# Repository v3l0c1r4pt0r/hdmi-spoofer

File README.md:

# HDMI EDID spoofer

Tiny HDMI board that optionally spoofs EDID data with contents of its own memory.

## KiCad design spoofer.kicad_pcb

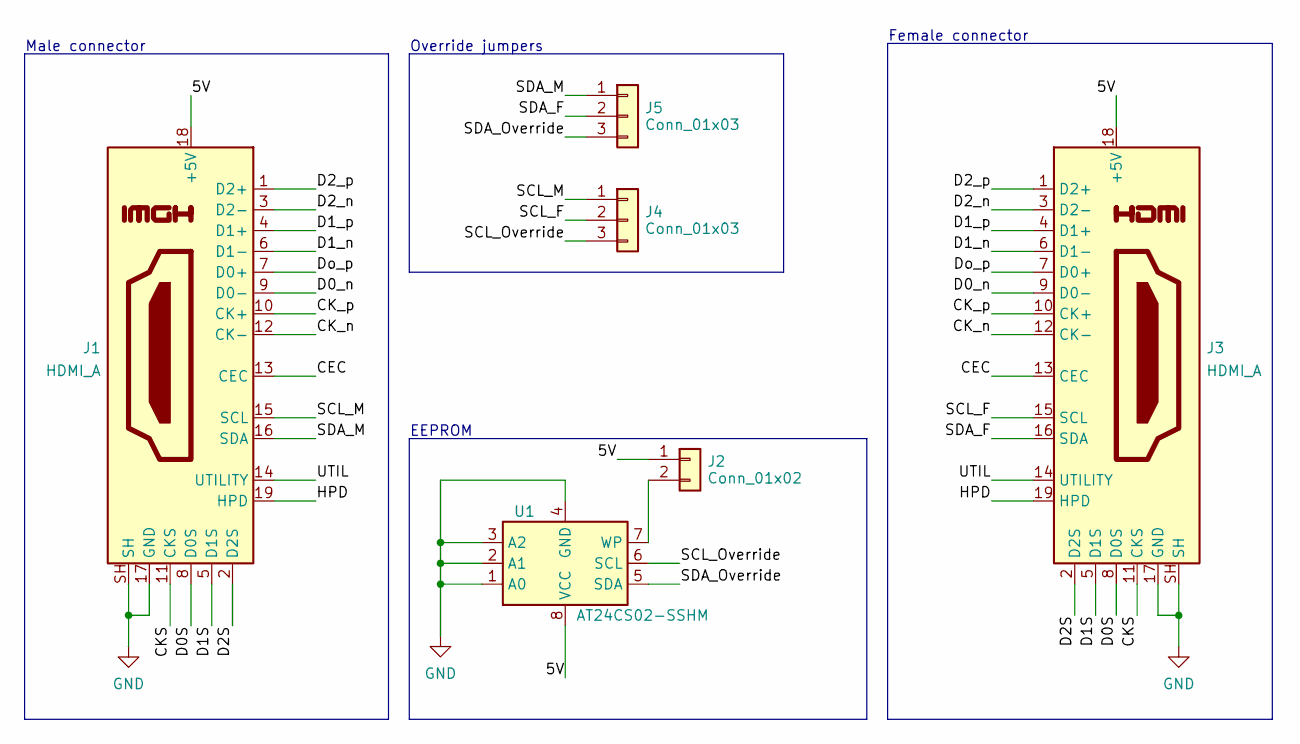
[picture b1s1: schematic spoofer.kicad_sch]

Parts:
J1: HDMI_A; HDMI_A_Contact_Technology_HDMI-19APL2_Horizontal
J2: Conn_01x02; PinHeader_1x02_P2.54mm_Vertical
J3: HDMI_A; 206A-SEAN-R03
J4, J5: Conn_01x03; PinHeader_1x03_P2.54mm_Vertical
U1: AT24CS02-SSHM; SOIC-8_3.9x4.9mm_P1.27mm; LCSC# C6205

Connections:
/5V: J1.18 (+5V), J2.1, J3.18 (+5V), U1.8 (VCC)
/CEC: J1.13 (CEC), J3.13 (CEC)
/CKS: J1.11 (CKS), J3.11 (CKS)
/CK_n: J1.12 (CK-), J3.12 (CK-)
/CK_p: J1.10 (CK+), J3.10 (CK+)
/D0S: J1.8 (D0S), J3.8 (D0S)
/D0_n: J1.9 (D0-), J3.9 (D0-)
/D1S: J1.5 (D1S), J3.5 (D1S)
/D1_n: J1.6 (D1-), J3.6 (D1-)
/D1_p: J1.4 (D1+), J3.4 (D1+)
/D2S: J1.2 (D2S), J3.2 (D2S)
/D2_n: J1.3 (D2-), J3.3 (D2-)
/D2_p: J1.1 (D2+), J3.1 (D2+)
/Do_p: J1.7 (D0+), J3.7 (D0+)
/HPD: J1.19 (HPD), J3.19 (HPD)
/SCL_F: J3.15 (SCL), J4.2
/SCL_M: J1.15 (SCL), J4.1
/SCL_Override: J4.3, U1.6 (SCL)
/SDA_F: J3.16 (SDA), J5.2
/SDA_M: J1.16 (SDA), J5.1
/SDA_Override: J5.3, U1.5 (SDA)
/UTIL: J1.14 (UTILITY), J3.14 (UTILITY)
GND: J1.17 (GND), J1.SH, J3.17 (GND), J3.SH, U1.1 (A0), U1.2 (A1), U1.3 (A2), U1.4 (GND)
unnamed: J2.2, U1.7 (WP)

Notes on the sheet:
Female connector
EEPROM
Override jumpers
Male connector

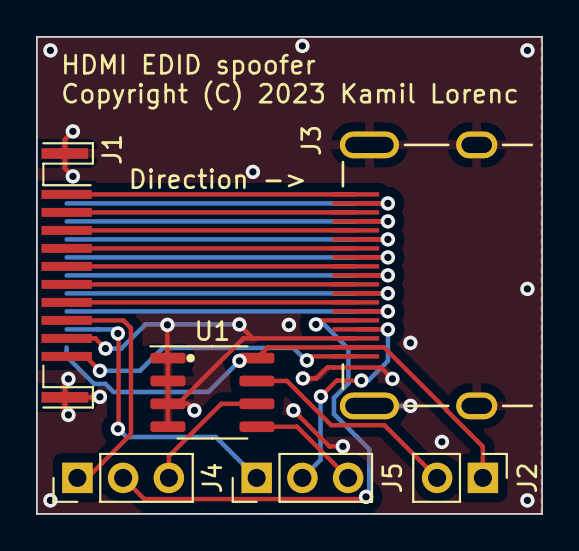
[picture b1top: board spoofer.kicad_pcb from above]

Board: 2 copper layers, 28.1 x 26.5 mm, 6 parts (0 on the bottom side), 24 nets.

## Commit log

2023-07-09 Initial empty repository
2023-07-09 Add finished schematics
2023-07-09 Add gitignore
2023-07-23 Redesign board
    Now it is smaller.
2023-07-23 Add silkscreen help
2024-01-02 Add finished project picture
2024-01-02 Fix picture size
    It was too big.
2024-01-02 Add footprint and symbol library as submodule
2024-01-02 Link footprint library to project

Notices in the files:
spoofer.kicad_pcb:
Copyright (C) 2023 Kamil Lorenc
